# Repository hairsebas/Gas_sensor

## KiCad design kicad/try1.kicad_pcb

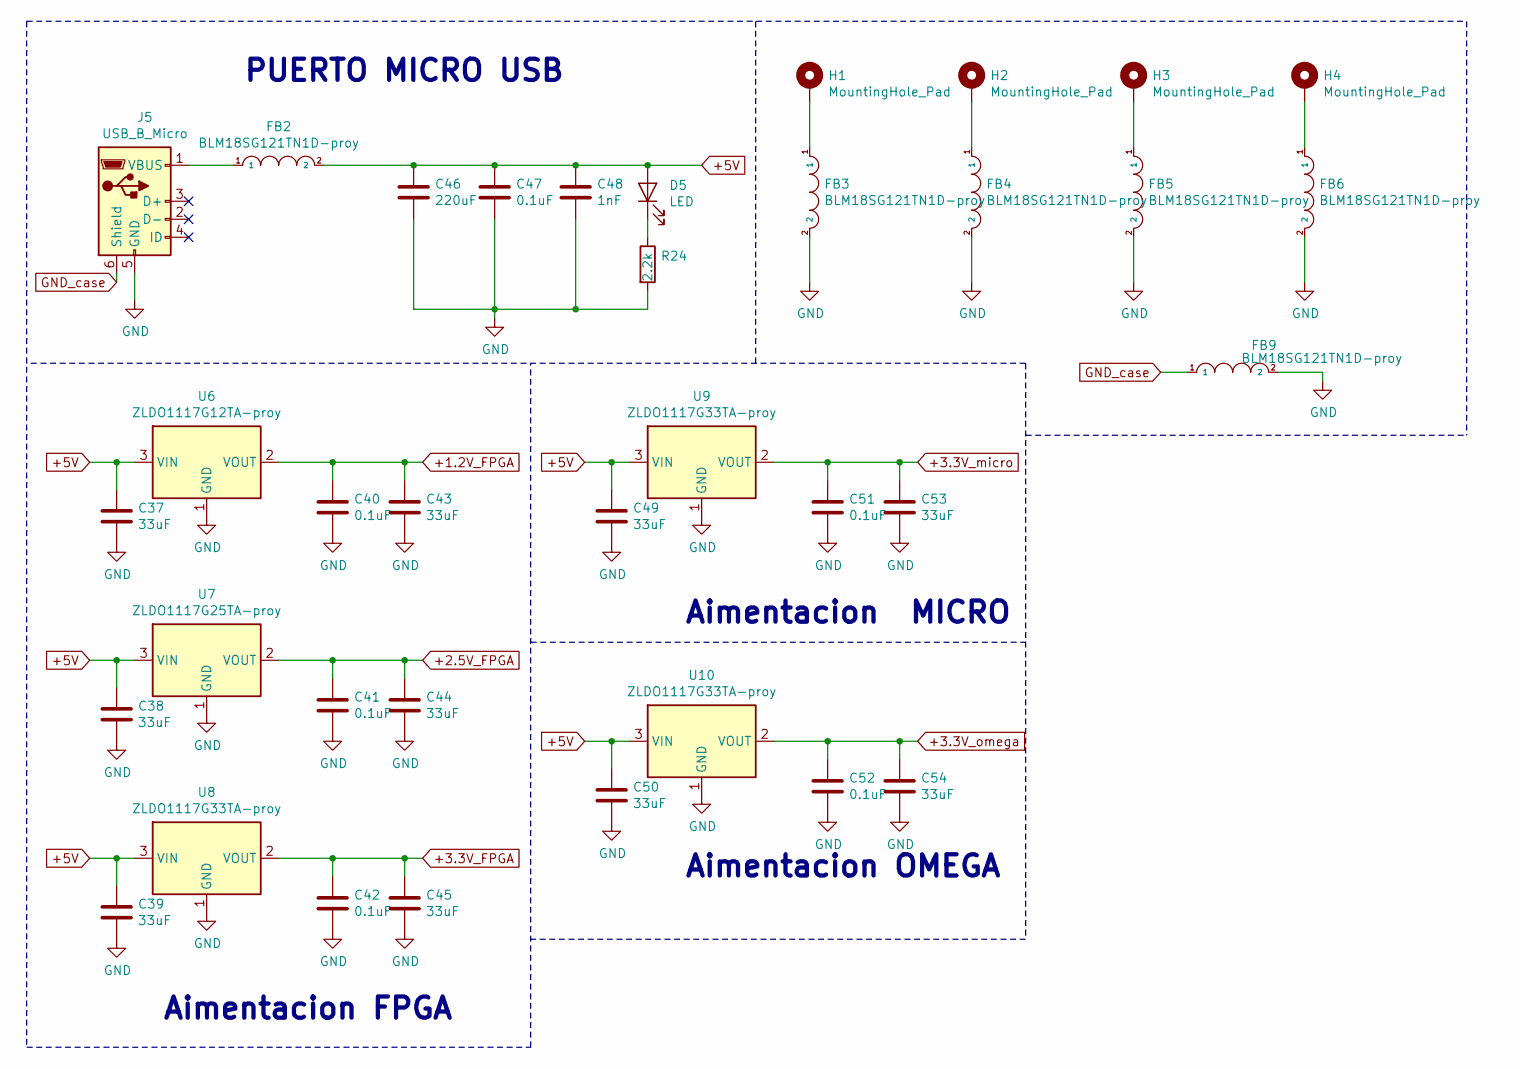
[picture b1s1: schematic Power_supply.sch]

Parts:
C37, C38, C39, C43, C44, C45, C49, C50, C53, C54: 33uF; R_0805_2012Metric_Pad1.15x1.40mm_HandSolder
C40, C41, C42, C47, C51, C52: 0.1uF; R_0603_1608Metric_Pad1.05x0.95mm_HandSolder
C46: 220uF; R_1206_3216Metric_Pad1.42x1.75mm_HandSolder
C48: 1nF; R_0603_1608Metric_Pad1.05x0.95mm_HandSolder
D5: LED; LED_0603_1608Metric_Pad1.05x0.95mm_HandSolder
FB2, FB3, FB4, FB5, FB6, FB9: BLM18SG121TN1D-proy; R_0603_1608Metric_Pad1.05x0.95mm_HandSolder; Manufacturer_Part_Number BLM18SG121TN1D; Mouser Part Number 81-BLM18SG121TN1D
H1, H2, H3, H4: MountingHole_Pad; MountingHole_2.5mm_Pad
J5: USB_B_Micro; USB_Micro-B_Wuerth_629105150521
R24: 2.2k; R_0603_1608Metric_Pad1.05x0.95mm_HandSolder
U6: ZLDO1117G12TA-proy; SOT-223
U7: ZLDO1117G25TA-proy; SOT-223
U8, U9, U10: ZLDO1117G33TA-proy; SOT-223

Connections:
+1.2V_FPGA: C40.1, C43.1, U6.2 (VOUT); also elsewhere on the board
+2.5V_FPGA: C41.1, C44.1, U7.2 (VOUT); also elsewhere on the board
+3.3V_FPGA: C42.1, C45.1, U8.2 (VOUT); also elsewhere on the board
+3.3V_micro: C51.1, C53.1, U9.2 (VOUT); also elsewhere on the board
+3.3V_omega: C52.1, C54.1, U10.2 (VOUT); also elsewhere on the board
+5V: C37.1, C38.1, C39.1, C46.1, C47.1, C48.1, C49.1, C50.1, D5.2 (A), FB2.2, U6.3 (VIN), U7.3 (VIN), U8.3 (VIN), U9.3 (VIN), U10.3 (VIN); also elsewhere on the board
GND: C37.2, C38.2, C39.2, C40.2, C41.2, C42.2, C43.2, C44.2, C45.2, C46.2, C47.2, C48.2, C49.2, C50.2, C51.2, C52.2, C53.2, C54.2, FB3.2, FB4.2, FB5.2, FB6.2, FB9.2, J5.5 (GND), R24.2, U6.1 (GND), U7.1 (GND), U8.1 (GND), U9.1 (GND), U10.1 (GND); also elsewhere on the board
GND_case: FB9.1, J5.6 (Shield)
unnamed: D5.1 (K), R24.1
unnamed: FB2.1, J5.1 (VBUS)
unnamed: FB3.1, H1.1
unnamed: FB4.1, H2.1
unnamed: FB5.1, H3.1
unnamed: FB6.1, H4.1

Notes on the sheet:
PUERTO MICRO USB
Aimentacion FPGA
Aimentacion MICRO
Aimentacion OMEGA

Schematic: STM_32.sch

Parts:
C25, C26, C27, C28, C30: 0.1uF; R_0603_1608Metric_Pad1.05x0.95mm_HandSolder
C29: 1uF; R_0603_1608Metric_Pad1.05x0.95mm_HandSolder
FB7: BLM18SG121TN1D-proy; R_0603_1608Metric_Pad1.05x0.95mm_HandSolder; Manufacturer_Part_Number BLM18SG121TN1D; Mouser Part Number 81-BLM18SG121TN1D
R15, R16, R17: 1k; R_0603_1608Metric_Pad1.05x0.95mm_HandSolder
U4: STM32F100RBT6B-proy; LQFP-64_10x10mm_P0.5mm

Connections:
+3.3V_micro: C25.1, C26.1, C27.1, C28.1, FB7.1, R15.1, U4.19, U4.32, U4.48, U4.64; also elsewhere on the board
/FPGA_ICE40UP5K/I2C_FPGA_SCL: U4.58; also elsewhere on the board
/FPGA_ICE40UP5K/I2C_FPGA_SDA: U4.59; also elsewhere on the board
/FPGA_ICE40UP5K/ICE40_CMISO: U4.22; also elsewhere on the board
/FPGA_ICE40UP5K/ICE40_CMOSI: U4.23; also elsewhere on the board
/FPGA_ICE40UP5K/ICE40_CSCK: U4.21; also elsewhere on the board
/FPGA_ICE40UP5K/ICE40_CSS: U4.20; also elsewhere on the board
/Onion_2/BOOT0: R16.1, U4.60; also elsewhere on the board
/Onion_2/BOOT1: R15.2, R17.2, U4.28; also elsewhere on the board
/Onion_2/JTAG0: U4.46; also elsewhere on the board
/Onion_2/JTAG1: U4.49; also elsewhere on the board
/Onion_2/JTAG2: U4.50; also elsewhere on the board
/Onion_2/JTAG3: U4.55; also elsewhere on the board
/Onion_2/JTAG4: U4.56; also elsewhere on the board
/STM_32/UART_M_RX: U4.52; also elsewhere on the board
/STM_32/UART_M_TX: U4.51; also elsewhere on the board
GND: C25.2, C26.2, C27.2, C28.2, C29.2, C30.2, R16.2, R17.1, U4.18, U4.31, U4.47, U4.63; also elsewhere on the board
unnamed: C29.1, C30.1, FB7.2, U4.13
unnamed 76: U4.12; also elsewhere on the board

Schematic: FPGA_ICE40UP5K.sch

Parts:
C1, C7: 0.01uF; R_0603_1608Metric_Pad1.05x0.95mm_HandSolder
C2, C5, C8, C21, C22, C24, C31, C55: 0.1uF; R_0603_1608Metric_Pad1.05x0.95mm_HandSolder
C3, C9, C20: 1uF; R_0603_1608Metric_Pad1.05x0.95mm_HandSolder
C4, C19, C23: 10uF; R_0603_1608Metric_Pad1.05x0.95mm_HandSolder
C10, C11, C12, C13, C15, C16, C17, C18: 33nF; R_0603_1608Metric_Pad1.05x0.95mm_HandSolder
C14: 22uF; R_0603_1608Metric_Pad1.05x0.95mm_HandSolder
D2: LED; LED_0603_1608Metric_Pad1.05x0.95mm_HandSolder
J1: Conn_02x11_Odd_Even; PinHeader_2x11_P2.54mm_Vertical
J2: Conn_01x08_Female; PinHeader_1x08_P2.54mm_Vertical
R1, R3, R4, R5, R6, R7, R8, R9, R10: 100; R_0603_1608Metric_Pad1.05x0.95mm_HandSolder
R2, R25: 2.2K; R_0603_1608Metric_Pad1.05x0.95mm_HandSolder
R11: 10k; R_0603_1608Metric_Pad1.05x0.95mm_HandSolder
R12, R13, R14: 10K; R_0603_1608Metric_Pad1.05x0.95mm_HandSolder
SW1: LL3301NF065QG-proy
U1: ICE40UP5K-SG48ITR50-proy; QFN-48-1EP_7x7mm_P0.5mm_EP5.6x5.6mm
U2: AD7918BRUZ-proy
U3: W25Q32JVSS-proy; SOIC127P790X216-8N-proy
X1: CWX823-025.0M-proy

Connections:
+1.2V_FPGA: C1.2, C2.2, C3.2, R1.2, U1.5, U1.30; also elsewhere on the board
+2.5V_FPGA: C20.2, U1.24, U2.7; also elsewhere on the board
+3.3V_FPGA: C7.2, C8.2, C9.2, C19.2, C21.2, C24.1, C31.2, C55.2, J1.1, R2.1, R11.2, R12.2, R14.2, U1.1, U1.22, U1.33, U2.19, U3.8, X1.4; also elsewhere on the board
+5V: C22.2, C23.2, U2.5, U2.6; also elsewhere on the board
/FPGA_ICE40UP5K/ADC_CS: U1.27, U2.3
/FPGA_ICE40UP5K/ADC_DIN: U1.26, U2.2
/FPGA_ICE40UP5K/ADC_DOUT: U1.28, U2.18
/FPGA_ICE40UP5K/ADC_SCLK: U1.25, U2.1
/FPGA_ICE40UP5K/CLK_IN: U1.20, X1.3
/FPGA_ICE40UP5K/CRESET_B: C14.1, R11.1, SW1.2, SW1.4, U1.8; also elsewhere on the board
/FPGA_ICE40UP5K/I2C_FPGA_SCL: U1.11; also elsewhere on the board
/FPGA_ICE40UP5K/I2C_FPGA_SDA: U1.12; also elsewhere on the board
/FPGA_ICE40UP5K/ICE40_CLK: U1.15, U3.6; also elsewhere on the board
/FPGA_ICE40UP5K/ICE40_CMISO: U1.19; also elsewhere on the board
/FPGA_ICE40UP5K/ICE40_CMOSI: U1.18; also elsewhere on the board
/FPGA_ICE40UP5K/ICE40_CS: R13.2, U1.16, U3.1; also elsewhere on the board
/FPGA_ICE40UP5K/ICE40_CSCK: U1.21; also elsewhere on the board
/FPGA_ICE40UP5K/ICE40_CSS: U1.23; also elsewhere on the board
/FPGA_ICE40UP5K/ICE40_MISO: U1.14, U3.5; also elsewhere on the board
/FPGA_ICE40UP5K/ICE40_MOSI: U1.17, U3.2; also elsewhere on the board
/FPGA_ICE40UP5K/PIO3: J1.3, U1.9
/FPGA_ICE40UP5K/PIO4: J1.4, U1.10
/FPGA_ICE40UP5K/PIO5: J1.5, U1.4
/FPGA_ICE40UP5K/PIO6: J1.6, U1.6
/FPGA_ICE40UP5K/PIO7: J1.7, U1.2
/FPGA_ICE40UP5K/PIO8: J1.8, U1.3
/FPGA_ICE40UP5K/PIO9: J1.9, U1.47
/FPGA_ICE40UP5K/PIO10: J1.10, U1.48
/FPGA_ICE40UP5K/PIO11: J1.11, U1.45
/FPGA_ICE40UP5K/PIO12: J1.12, U1.46
/FPGA_ICE40UP5K/PIO13: J1.13, U1.43
/FPGA_ICE40UP5K/PIO14: J1.14, U1.44
/FPGA_ICE40UP5K/PIO15: J1.15, U1.38
/FPGA_ICE40UP5K/PIO16: J1.16, U1.42
/FPGA_ICE40UP5K/PIO17: J1.17, U1.36
/FPGA_ICE40UP5K/PIO18: J1.18, U1.37
/FPGA_ICE40UP5K/PIO19: J1.19, U1.34
/FPGA_ICE40UP5K/PIO20: J1.20, U1.35
/FPGA_ICE40UP5K/PIO21: J1.21, U1.31
/FPGA_ICE40UP5K/PIO22: J1.22, U1.32
GND: C1.1, C2.1, C3.1, C4.1, C5.1, C7.1, C8.1, C9.1, C10.1, C11.1, C12.1, C13.1, C14.2, C15.1, C16.1, C17.1, C18.1, C19.1, C20.1, C21.1, C22.1, C23.1, C24.2, C31.1, C55.1, D2.1 (K), J1.2, R13.1, R25.2, SW1.1, SW1.3, U1.49, U2.4, U2.8, U2.17, U2.20, U3.4, X1.2; also elsewhere on the board
unnamed: C4.2, C5.2, R1.1, U1.29
unnamed: C10.2, R10.1, U2.9
unnamed: C11.2, R9.1, U2.10
unnamed: C12.2, R8.1, U2.11
unnamed: C13.2, R7.1, U2.12
unnamed: C15.2, R6.1, U2.13
unnamed: C16.2, R5.1, U2.14
unnamed: C17.2, R4.1, U2.15
unnamed: C18.2, R3.1, U2.16
unnamed: D2.2 (A), R2.2, U1.7
unnamed: J2.1, R3.2
unnamed: J2.2, R4.2
unnamed: J2.3, R5.2
unnamed: J2.4, R6.2
unnamed: J2.5, R7.2
unnamed: J2.6, R8.2
unnamed: J2.7, R9.2
unnamed: J2.8, R10.2
unnamed: R12.1, U3.7
unnamed: R14.1, U3.3
unnamed: R25.1, X1.1

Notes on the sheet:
FPGA
ADC
MEMORIA FLASH
RESET
OSCILADOR

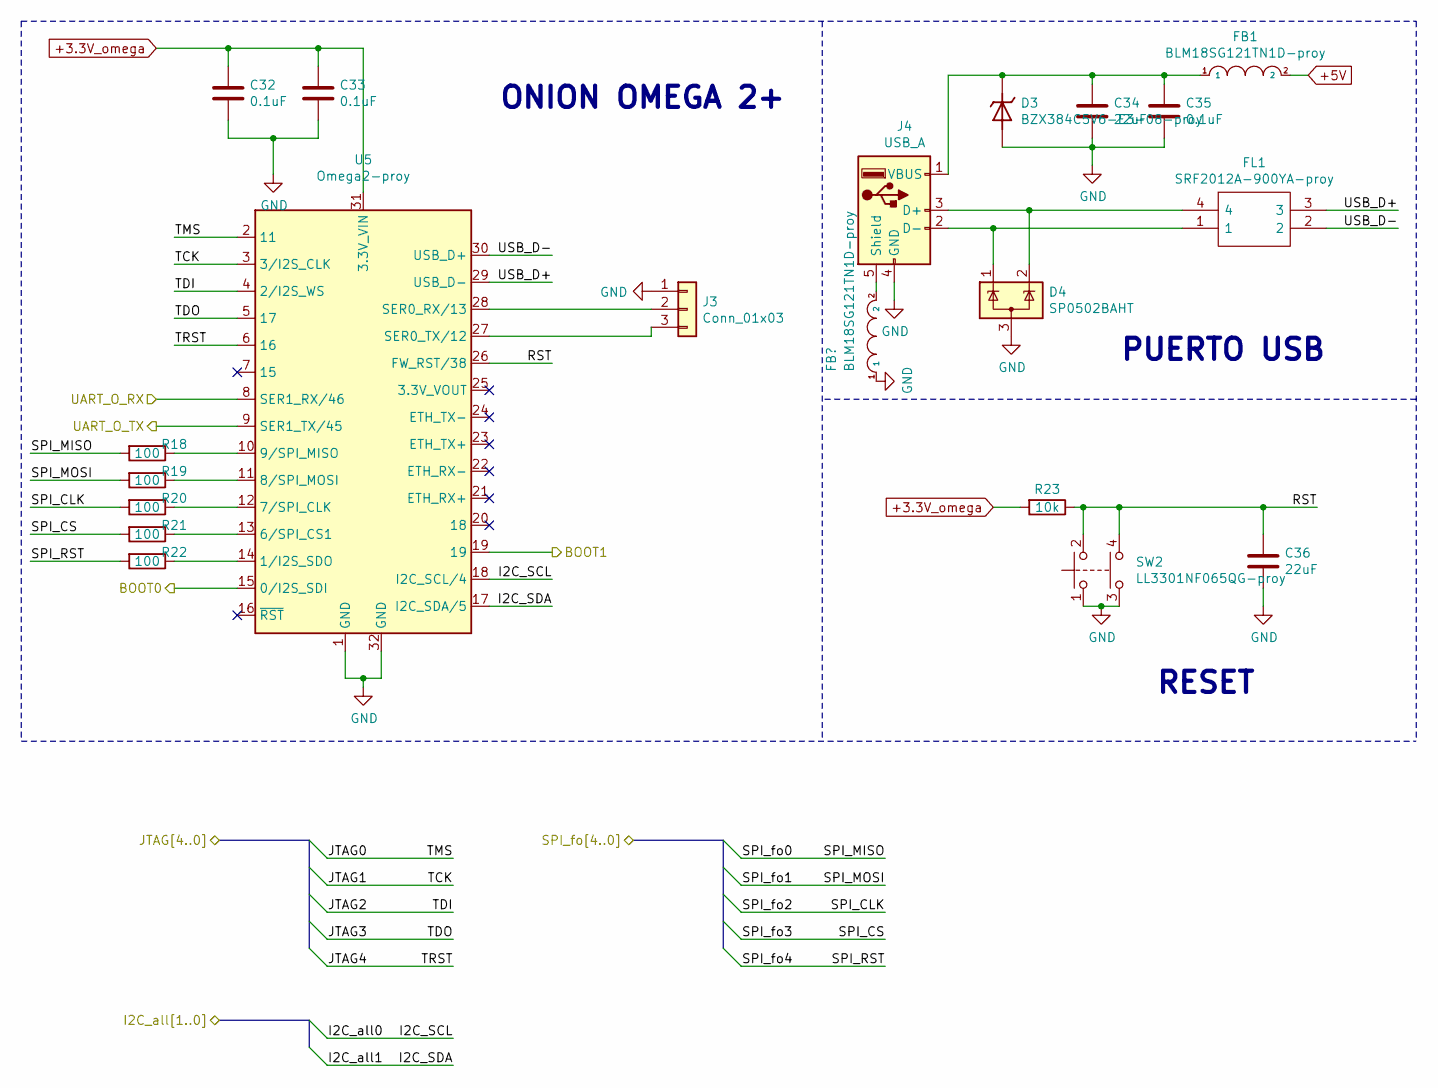
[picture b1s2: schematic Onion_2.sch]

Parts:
C32, C33, C35: 0.1uF; R_0603_1608Metric_Pad1.05x0.95mm_HandSolder
C34, C36: 22uF; R_0603_1608Metric_Pad1.05x0.95mm_HandSolder
D3: BZX384C5V6-E3-08-proy; SOD-323-proy
D4: SP0502BAHT; SOT-23
FB1: BLM18SG121TN1D-proy; R_0603_1608Metric_Pad1.05x0.95mm_HandSolder; Manufacturer_Part_Number BLM18SG121TN1D; Mouser Part Number 81-BLM18SG121TN1D
FL1: SRF2012A-900YA-proy; SRF2012A900YA_proy; Manufacturer_Part_Number SRF2012A-900YA; Mouser Part Number 652-SRF2012A-900YA
J3: Conn_01x03; PinHeader_1x03_P2.54mm_Vertical
J4: USB_A; USB_A_Stewart_SS-52100-001_Horizontal
R18, R19, R20, R21, R22: 100; R_0603_1608Metric_Pad1.05x0.95mm_HandSolder
R23: 10k; R_0603_1608Metric_Pad1.05x0.95mm_HandSolder
SW2: LL3301NF065QG-proy
U5: Omega2-proy; Onion_Omega2+

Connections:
+3.3V_omega: C32.1, C33.1, R23.2, U5.31 (3.3V_VIN); also elsewhere on the board
+5V: FB1.2; also elsewhere on the board
/FPGA_ICE40UP5K/CRESET_B: R22.2; also elsewhere on the board
/FPGA_ICE40UP5K/I2C_FPGA_SCL: U5.18 (I2C_SCL/4); also elsewhere on the board
/FPGA_ICE40UP5K/I2C_FPGA_SDA: U5.17 (I2C_SDA/5); also elsewhere on the board
/FPGA_ICE40UP5K/ICE40_CLK: R20.2; also elsewhere on the board
/FPGA_ICE40UP5K/ICE40_CS: R21.2; also elsewhere on the board
/FPGA_ICE40UP5K/ICE40_MISO: R18.2; also elsewhere on the board
/FPGA_ICE40UP5K/ICE40_MOSI: R19.2; also elsewhere on the board
/Onion_2/BOOT0: U5.15 (0/I2S_SDI); also elsewhere on the board
/Onion_2/BOOT1: U5.19; also elsewhere on the board
/Onion_2/JTAG0: U5.2 (11); also elsewhere on the board
/Onion_2/JTAG1: U5.3 (3/I2S_CLK); also elsewhere on the board
/Onion_2/JTAG2: U5.4 (2/I2S_WS); also elsewhere on the board
/Onion_2/JTAG3: U5.5 (17); also elsewhere on the board
/Onion_2/JTAG4: U5.6 (16); also elsewhere on the board
/Onion_2/RST: C36.1, R23.1, SW2.2, SW2.4, U5.26 (FW_RST/38)
/Onion_2/USB_D+: FL1.3, U5.29 (USB_D-)
/Onion_2/USB_D-: FL1.2, U5.30 (USB_D+)
/STM_32/UART_M_RX: U5.9 (SER1_TX/45); also elsewhere on the board
/STM_32/UART_M_TX: U5.8 (SER1_RX/46); also elsewhere on the board
GND: C32.2, C33.2, C34.2, C35.2, C36.2, D3.A, D4.3 (A), J3.1, J4.4 (GND), SW2.1, SW2.3, U5.1 (GND), U5.32 (GND); also elsewhere on the board
unnamed: C34.1, C35.1, D3.C, FB1.1, J4.1 (VBUS)
unnamed: D4.1 (K), FL1.1, J4.2 (D-)
unnamed: D4.2 (K), FL1.4, J4.3 (D+)
unnamed 77: J4.5 (Shield); also elsewhere on the board
unnamed: J3.2, U5.28 (SER0_RX/13)
unnamed: J3.3, U5.27 (SER0_TX/12)
unnamed: R18.1, U5.10 (9/SPI_MISO)
unnamed: R19.1, U5.11 (8/SPI_MOSI)
unnamed: R20.1, U5.12 (7/SPI_CLK)
unnamed: R21.1, U5.13 (6/SPI_CS1)
unnamed: R22.1, U5.14 (1/I2S_SDO)

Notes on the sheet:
ONION OMEGA 2+
PUERTO USB
RESET

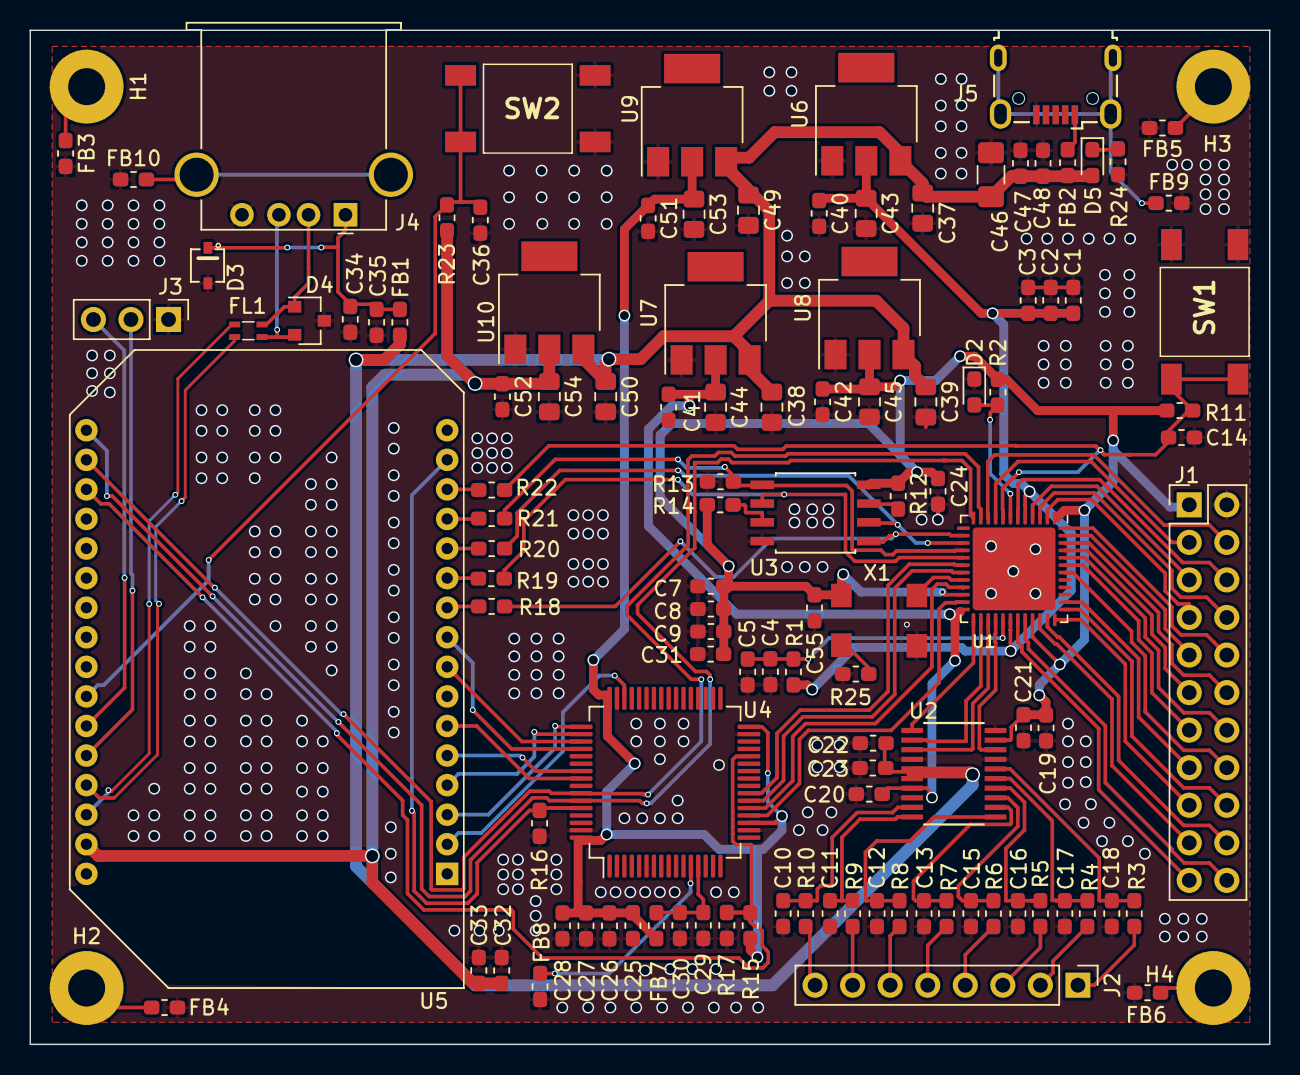
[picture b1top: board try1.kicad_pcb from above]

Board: 2 copper layers, 83.8 x 68.6 mm, 116 parts (0 on the bottom side), 96 nets.

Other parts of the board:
FB8, FB10: BLM18SG121TN1D-proy; R_0603_1608Metric_Pad1.05x0.95mm_HandSolder

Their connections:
GND: FB8.1, FB10.1; also elsewhere on the board
unnamed 76: FB8.2; also elsewhere on the board
unnamed 77: FB10.2; also elsewhere on the board

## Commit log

2020-04-14 Remove duplicated directory
2020-04-14 Create kicad

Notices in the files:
parts and their libraries:
Copyright 2016 Accelerated Designs. All rights reserved.
